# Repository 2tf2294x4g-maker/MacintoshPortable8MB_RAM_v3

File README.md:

# Mac Portable 8MB RAM Card (v3 — All-5V)

Expands a Macintosh Portable to **9 MB total** (1 MB onboard + 8 MB this card) — the maximum the Portable's address space supports.

All-5V design using 1M×8 SRAM chips and an ATF1502ASL CPLD. Works with both the **M5120** (non-backlit) and **M5126** (backlit) Portable via the MODEL jumper. Banks are added sequentially — no jumpers needed as you populate.

> ⚠️ **PRE-PRODUCTION — NOT TESTED**
> This board has been designed and ordered but has not yet been assembled or validated on real hardware. Schematics, firmware, and Gerbers are provided as-is. Do not build for production use until hardware validation is complete.

---

## What's new in v3 vs v2

| | v2 | v3 |
|---|---|---|
| Model compatibility | M5120 only | M5120 + M5126 (MODEL jumper) |
| Bank indicator | none | 4 green latching LEDs (one per bank) |
| Ghost RAM protection | none | 10 KΩ pull-downs on SD0–SD15 |
| Population jumper | SIZE jumper (JP1) | none — sequential by design |
| DTACK output | bodge wire to CPLD pad | J3 header (pin 1 = /DTACK, pin 2 = /EXT_DTACK) |
| SRAM count | 8× AS6C8008 | 8× AS6C8008 (same chips) |

---

## Specs

| | |
|---|---|
| Capacity | 8 MB (8× 1M×8 SRAM) |
| System total | 9 MB M5120 (open) / 7 MB M5126 (closed) |
| Bus width | 16-bit (two 8-bit SRAMs per bank) |
| Banks | 4 × 2 MB, populated sequentially |
| Logic | ATF1502ASL CPLD (5V, TQFP-44) |
| SRAM | 8× AS6C8008-55ZIN (5V, TSOP-II-44) |
| Layers | 4 (F.Cu signal / GND plane / +5V plane / B.Cu signal) |
| Connector | Samtec BCS-125-F-D-HE (50-pin 2×25, horizontal entry) |
| MODEL jumper | JP1: OPEN = M5120 non-backlit (9 MB) / CLOSED = M5126 backlit (7 MB) |

---

## Bill of Materials

| Ref | Qty | Value | Package | Part / Notes |
|-----|----:|-------|---------|--------------|
| U1–U8 | 8 | AS6C8008-55ZIN | TSOP-II-44 | Alliance Memory — 1M×8 5V SRAM 55 ns. Order spares. |
| U9 | 1 | ATF1502ASL | TQFP-44 | Microchip ATF1502ASL-**25AU44** — must be **ASL** (5V), not ASV |
| U10, U11 | 2 | 74HC245 | SOIC-20 **wide** | SN74HC245**DW** — verify wide (7.5 mm) body |
| J1 | 1 | RAM connector | Samtec BCS-125-F-D-HE | 50-pin socket, horizontal entry |
| J2 | 1 | JTAG header | 1×6 2.54 mm pin header | GND/VCC/TDO/TDI/TMS/TCK left-to-right |
| J3 | 1 | PDS DTACK header | 1×2 2.54 mm pin header | Pin 1 = /DTACK → PDS B7, Pin 2 = /EXT_DTACK → PDS B30 |
| JP1 | 1 | MODEL jumper | 1×2 2.54 mm pin header + shunt | OPEN = M5120 / CLOSED = M5126 |
| D1–D4 | 4 | Green LED | 0603 | Latch ON at boot when each bank is confirmed by the CPLD |
| R1–R4 | 4 | 330 Ω | 0402 | Series resistors for D1–D4 |
| R5–R20 | 16 | 10 KΩ | 0402 | Pull-downs on SD0–SD15 (SRAM side of 74HC245) — prevent ghost RAM |
| R21–R24 | 4 | 10 KΩ | 0805 | Pull-ups on CPLD unused inputs and MODEL jumper pin |
| C1–C14 | 14 | 100 nF | 0805 | X7R 50V ceramic bypass (one per IC) |
| C15–C19 | 5 | 10 µF | 0805 | X5R 16V ceramic bulk |

Full BOM: [PortableRAM-8MB-v3-BOM.csv](PortableRAM-8MB-v3-BOM.csv)

---

## ⚠️ Important — SRAM Pinout

The AS6C8008 (1M×8) and AS7C4096A (512K×8 used in the 4MB card) are **both TSOP-II-44 but have different pinouts**. Do not mix them between boards.

---

## Population Guide

Banks are populated sequentially — each pair of SRAMs adds 2 MB. No jumpers required.

| Step | Chips | Total RAM |
|------|-------|-----------|
| 1 | U1 + U5 | 2 MB |
| 2 | U2 + U6 | 4 MB |
| 3 | U3 + U7 | 6 MB |
| 4 | U4 + U8 | 8 MB |

The green LED for each bank (D1–D4) latches on at boot when the CPLD confirms that bank is active. A dark LED means the bank is not yet populated.

---

## MODEL Jumper (JP1)

| JP1 | Portable model | System RAM |
|-----|---------------|-----------|
| Open (no shunt) | M5120 non-backlit | 9 MB |
| Closed (shunt installed) | M5126 backlit | 7 MB |

The M5126 uses slot CS0 for its backlight controller, which conflicts with the top 2 MB bank. Closing JP1 disables that bank so the two don't fight. Leave open for M5120.

---

## Files

```
PortableRAM-8MB.kicad_pcb     — PCB layout (KiCad 9)
PortableRAM-8MB.kicad_sch     — Schematic
PortableRAM-8MB.kicad_pro     — Project file
PortableRAM.kicad_sym         — Custom symbol library
PortableRAM.pretty/           — Custom footprint library
Library.pretty/               — Additional footprints
Gerbers/                      — Gerber + drill files (ready to order)
PortableRAM-8MB-v3-Gerbers.zip — Same, zipped (upload directly to fab)
firmware/
  PortableRAM8_v3.pld            — CUPL source (ATF1502ASL logic)
  PortableRAM8_v3.jed            — Compiled JEDEC fusemap
  PortableRAM8_v3.svf            — SVF for OpenOCD programming
  PortableRAM8_v3.fit            — WinCUPL fit report
  program.sh                  — One-command programming script (Tigard)
  BUILD.md                    — Firmware build instructions (WinCUPL + Wine)
PortableRAM-8MB-v3-BOM.csv
```

---

## Ordering the PCB

Upload `PortableRAM-8MB-v3-Gerbers.zip` to your preferred fab (JLCPCB, PCBWay, OSHPark, etc.).

**Board settings:**
- Layers: **4**
- Thickness: 1.6 mm
- Surface finish: **ENIG** (recommended — fine-pitch 0.8 mm pads on TSOP-II-44 and TQFP-44)
- All other settings: fab defaults

---

## Assembly Notes

Solder in this order:

1. **U9** (ATF1502ASL CPLD, TQFP-44) — center first, then drag-solder
2. **U1–U8** (SRAM, TSOP-II-44) — fine pitch; flux generously. Populate in bank pairs: U1+U5 → U2+U6 → U3+U7 → U4+U8
3. **U10, U11** (74HC245, SOIC-20 wide)
4. **R5–R20** (10 KΩ 0402 pull-downs)
5. **R1–R4** (330 Ω 0402 LED resistors)
6. **R21–R24** (10 KΩ 0805 pull-ups)
7. **C1–C14** (100 nF 0805 bypass caps)
8. **C15–C19** (10 µF 0805 bulk caps)
9. **D1–D4** (green 0603 LEDs — observe polarity)
10. **JP1** (1×2 header — add shunt for M5126, leave open for M5120)
11. **J2** (1×6 JTAG header)
12. **J3** (1×2 PDS DTACK header — on board edge)
13. **J1** (Samtec connector) — last

---

## Programming the CPLD

The ATF1502ASL must be programmed before the card will work. Use J2 (1×6 header on the board edge).

### J2 pinout (left to right, component side)

| Pin | Signal |
|-----|--------|
| 1 | GND |
| 2 | VCC |
| 3 | TDO |
| 4 | TDI |
| 5 | TMS |
| 6 | TCK |

### With a Tigard programmer (FT2232H-based)

Set the Tigard voltage jumper to **5V** before connecting.

```bash
cd firmware
./program.sh PortableRAM8_v3.svf
```

Success output ends with `shutdown command invoked` and no TDO mismatch errors.

See [firmware/BUILD.md](firmware/BUILD.md) for the full build and programming pipeline (WinCUPL + Wine on Linux, prjbureau for SVF generation).

---

## Installation

1. Power off and unplug the Mac Portable.
2. Remove the battery and bottom cover.
3. Set JP1 (MODEL jumper) for your machine — open for M5120, closed for M5126.
4. Seat the card on the RAM expansion header — J1 is a friction-fit horizontal-entry socket.
5. Reassemble and power on.

With a full build (all 8 SRAMs), you should see **9 MB** in About This Macintosh (M5120) or **7 MB** (M5126). All four green LEDs D1–D4 will be lit.

### DTACK Performance Fix — J3 header

The Mac Portable's GLU chip generates /DTACK for the 68000 with region-dependent timing:

| Address range | GLU /DTACK | Condition |
|---|---|---|
| 0x000000–0x4FFFFF | 2 clocks | Always — hardwired fast path |
| 0x500000–0x8FFFFF | 6 clocks | Normal operation (register configured) |
| 0x500000–0x8FFFFF | 18 clocks | After sleep/wake (register reset) |

The 8 MB card spans 0x100000–0x8FFFFF, straddling the split. Banks 0–1 (0x100000–0x4FFFFF) already get the GLU's 2-clock fast path. Banks 2–3 (0x500000–0x8FFFFF) run at 6 clocks and collapse to 18 clocks after sleep/wake when the GLU's DTACK register loses its configuration.

The fix is built into v3: the CPLD asserts /DTACK directly via **J3 pin 1**, bypassing the GLU for all card accesses. Connect a wire from J3 pin 1 to **PDS slot pin B7** (/DTACK) on the Mac Portable motherboard. The CPLD's path is purely combinatorial — faster than even the GLU's 2-clock mode — and immune to sleep/wake state loss.

J3 pin 2 (/EXT_DTACK → PDS B30) is an optional second output for experimentation.

**Validated on v2 hardware (July 2026):**

| Configuration | Speedometer | Snooper | Post-sleep |
|---|---|---|---|
| 1 MB card (baseline) | 1.990 | 87% | 1.985 |
| 8 MB card — no DTACK fix | 1.486 | 51% | 0.974 / 22% |
| **8 MB card + CPLD DTACK** | **2.170** | **102%** | **2.170** |
| **4 MB card + CPLD DTACK** | **2.170** | **102%** | **2.170** |

The CPLD outperforms the GLU's fastest mode (102% vs 87% baseline) because its combinatorial propagation delay is well under one bus clock. Post-sleep collapse is fully eliminated. The 4 MB result confirms the CPLD path is faster than even the GLU's hardwired 2-clock mode — the fix benefits all bank configurations, not just the upper 8 MB range.

The PDS connector is the 96-pin DIN-41612 on the Mac Portable motherboard (3 rows A/B/C, 32 pins each). Pin B7 is in row B, position 7 from the component side.

---

## References & Acknowledgements

**Dynamic Engineering Mac Portable RAM Card**
The address decode and bus control logic in `PortableRAM8_v3.pld` is derived from GAL22V10 PLD source files originally written for the Dynamic Engineering commercial RAM expansion card. These files define the core signal equations — bank chip-select generation, byte-lane write control via UDS*/LDS*, bus transceiver direction, and output enable timing. The original `.PLD` files were recovered and shared by *techknight* on the TinkerDifferent forum and #skunkworks Discord. Translated here from three GAL22V10 chips to a single ATF1502ASL CPLD, with corrections to the `r_w_u` equation and address decode base, and extended for 8MB capacity and M5126 compatibility.

**miejas — Macintosh Portable 4MB Memory Expansion**
[https://github.com/miejas/Macintosh-Portable-4-MB-Memory-Expansion](https://github.com/miejas/Macintosh-Portable-4-MB-Memory-Expansion)
Open-source 4MB RAM card used as a cross-reference for connector pinout, bus transceiver approach, and firmware structure.

**Reza Fouladian — PortableRAM BGA 8MB**
[https://github.com/rezafouladian/PortableRAM-BGA-8MB](https://github.com/rezafouladian/PortableRAM-BGA-8MB)
BGA-format 8MB card using the ATF1502ASV (3.3V CPLD) and SN74LVC4245A level translators. Reference for the 8MB address decode strategy and CPLD pin planning. Reza also provided direct guidance on driving /DTACK from the CPLD and on the Mac Portable PDS connector pinout — specifically confirming that /DTACK is available on PDS pin B7 and can be driven directly from a CPLD output. This insight is the basis for the J3 DTACK header on v3 and the validated bodge fix on v2.

**Apple Mac Portable Developer Notes & Schematics**
Apple's original hardware documentation for the Mac Portable expansion bus, memory map, and GLU register behaviour (including the $FC0200 DTACK register).

---

## License

Hardware released under [CERN-OHL-S v2](https://ohwr.org/cern_ohl_s_v2.txt). Firmware source (`PortableRAM8_v3.pld`) released under MIT.

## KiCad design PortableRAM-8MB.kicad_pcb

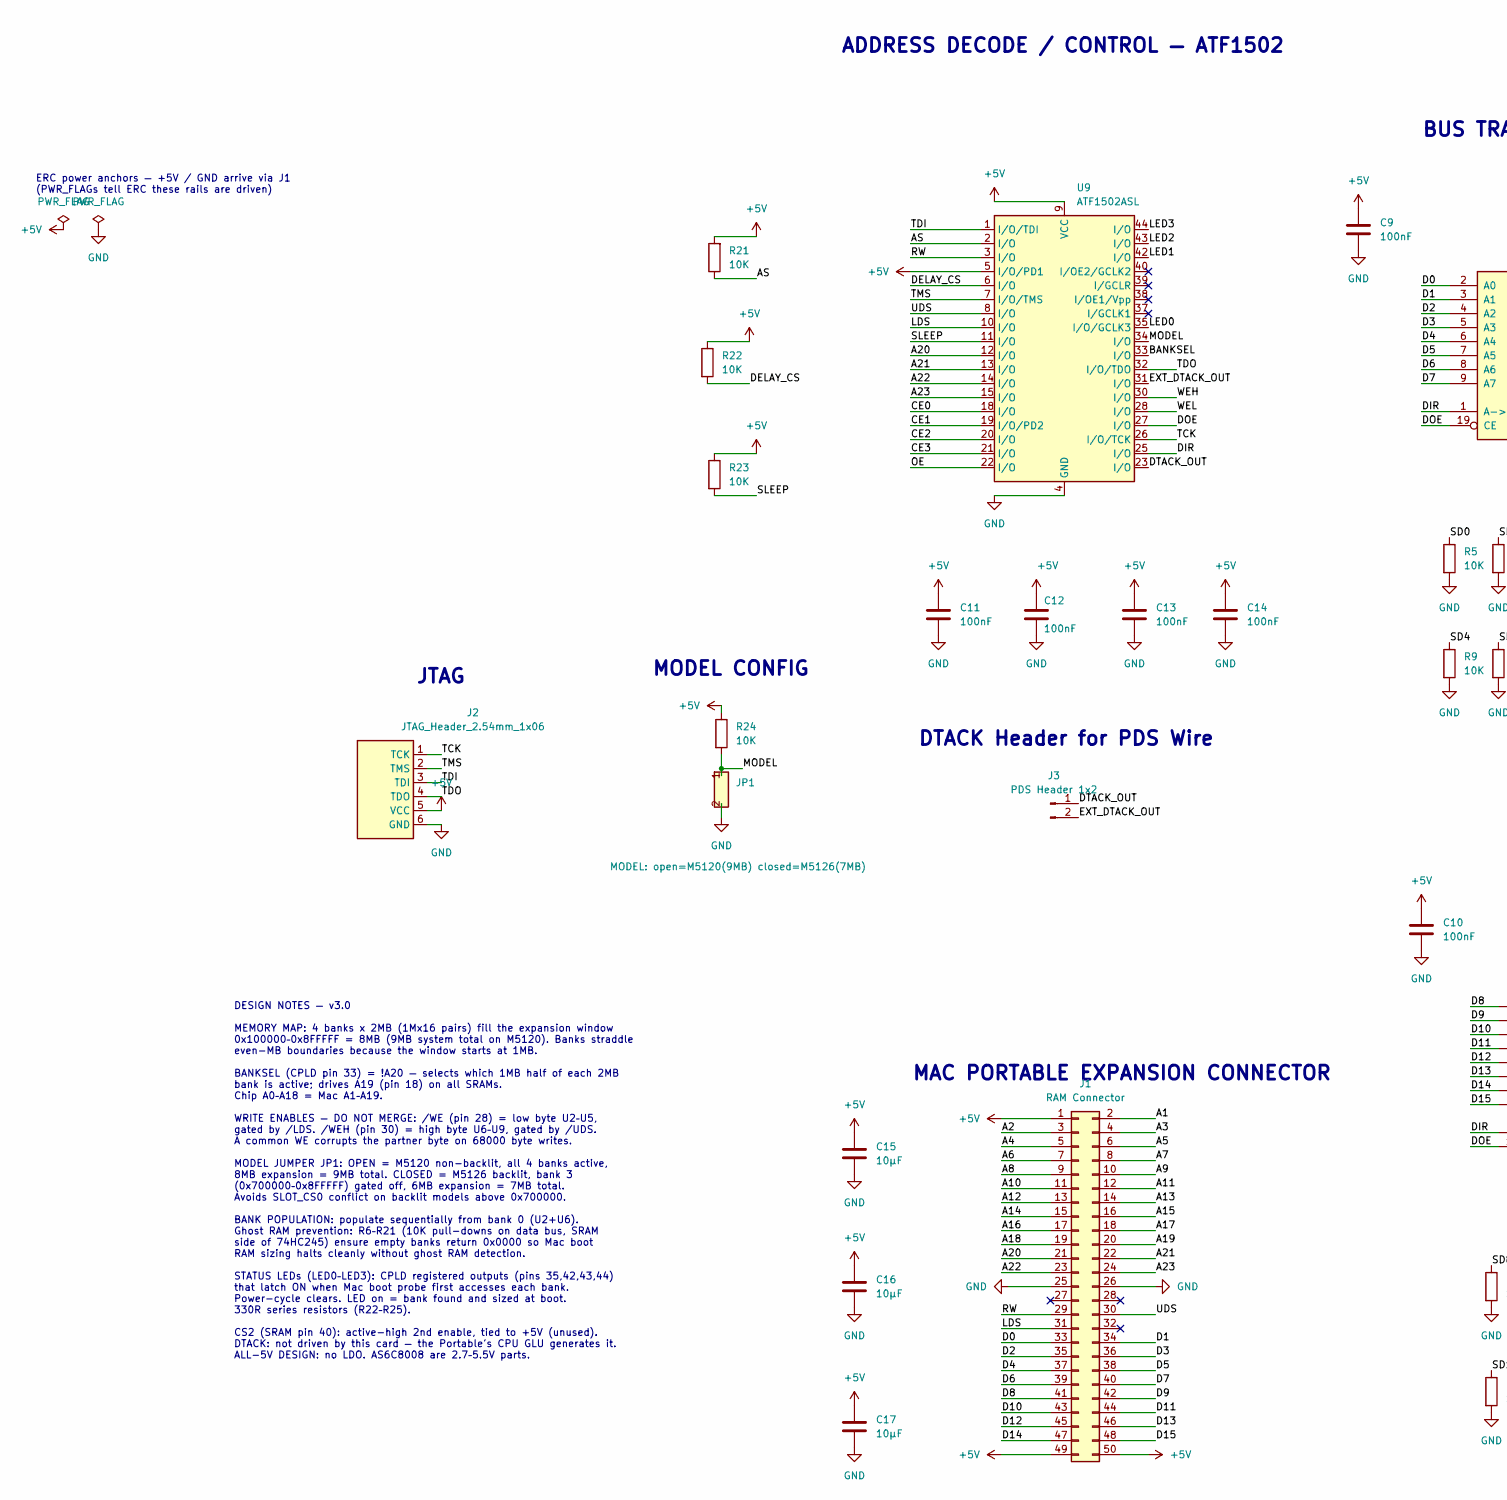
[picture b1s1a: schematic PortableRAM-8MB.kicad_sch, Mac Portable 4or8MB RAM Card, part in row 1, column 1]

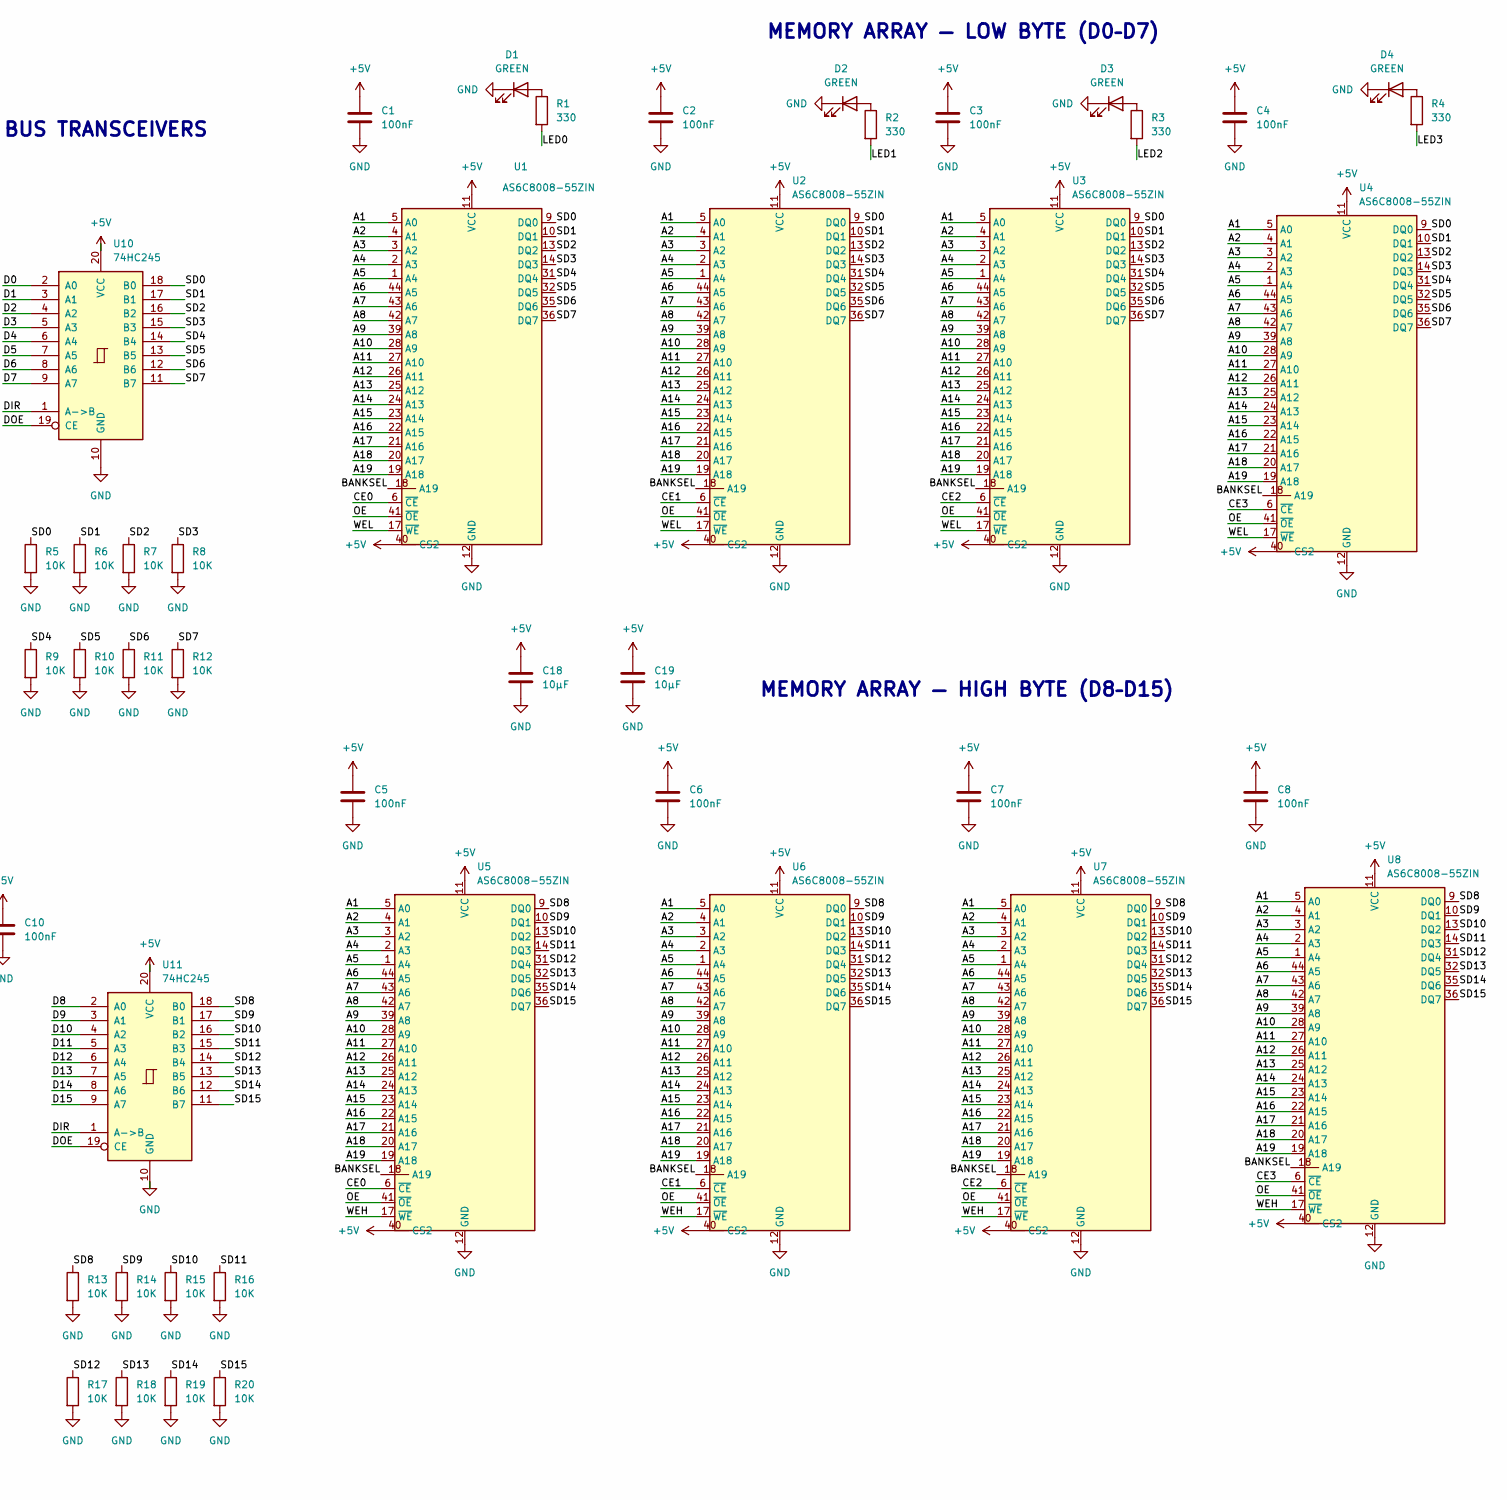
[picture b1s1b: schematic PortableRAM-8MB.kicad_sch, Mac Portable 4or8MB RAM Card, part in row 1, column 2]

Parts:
C1, C2, C3, C4, C5, C6, C7, C8, C9, C10, C11, C12, C13, C14: 100nF; C_0805_2012Metric
C15, C16, C17, C18, C19: 10µF; C_0805_2012Metric
D1, D2, D3, D4: GREEN; LED_0603_1608Metric
J1: RAM Connector; Samtec_BCS-125-F-D-HE
J2: JTAG_Header_2.54mm_1x06; PinHeader_1x06_P2.54mm_Vertical
J3: PDS Header 1x2; PinHeader_1x02_P2.54mm_Vertical
JP1: MODEL: open=M5120(9MB) closed=M5126(7MB); PinHeader_1x02_P2.54mm_Vertical
R1, R2, R3, R4: 330; R_0402_1005Metric
R5, R6, R7, R8, R9, R10, R11, R12, R13, R14, R15, R16, R17, R18, R19, R20: 10K; R_0402_1005Metric
R21, R22, R23, R24: 10K; R_0805_2012Metric
U1, U2, U3, U4, U5, U6, U7, U8: AS6C8008-55ZIN; TSOP-II-44_10.16x18.41mm_P0.8mm
U9: ATF1502ASL; TQFP-44_10x10mm_P0.8mm
U10, U11: 74HC245; SOIC-20W_7.5x12.8mm_P1.27mm

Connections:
+5V: C1.1, C2.1, C3.1, C4.1, C5.1, C6.1, C7.1, C8.1, C9.1, C10.1, C11.1, C12.1, C13.1, C14.1, C15.1, C16.1, C17.1, C18.1, C19.1, J1.1, J1.49, J1.50, J2.5 (VCC), R21.2, R22.1, R23.1, R24.1, U1.11 (VCC), U1.33 (VCC), U1.40 (CS2), U2.11 (VCC), U2.33 (VCC), U2.40 (CS2), U3.11 (VCC), U3.33 (VCC), U3.40 (CS2), U4.11 (VCC), U4.33 (VCC), U4.40 (CS2), U5.11 (VCC), U5.33 (VCC), U5.40 (CS2), U6.11 (VCC), U6.33 (VCC), U6.40 (CS2), U7.11 (VCC), U7.33 (VCC), U7.40 (CS2), U8.11 (VCC), U8.33 (VCC), U8.40 (CS2), U9.5 (I/O/PD1), U9.9 (VCC), U9.17 (VCC), U9.29 (VCC), U9.41 (VCC), U10.20 (VCC), U11.20 (VCC)
/A1: J1.2, U1.5 (A0), U2.5 (A0), U3.5 (A0), U4.5 (A0), U5.5 (A0), U6.5 (A0), U7.5 (A0), U8.5 (A0)
/A2: J1.3, U1.4 (A1), U2.4 (A1), U3.4 (A1), U4.4 (A1), U5.4 (A1), U6.4 (A1), U7.4 (A1), U8.4 (A1)
/A3: J1.4, U1.3 (A2), U2.3 (A2), U3.3 (A2), U4.3 (A2), U5.3 (A2), U6.3 (A2), U7.3 (A2), U8.3 (A2)
/A4: J1.5, U1.2 (A3), U2.2 (A3), U3.2 (A3), U4.2 (A3), U5.2 (A3), U6.2 (A3), U7.2 (A3), U8.2 (A3)
/A5: J1.6, U1.1 (A4), U2.1 (A4), U3.1 (A4), U4.1 (A4), U5.1 (A4), U6.1 (A4), U7.1 (A4), U8.1 (A4)
/A6: J1.7, U1.44 (A5), U2.44 (A5), U3.44 (A5), U4.44 (A5), U5.44 (A5), U6.44 (A5), U7.44 (A5), U8.44 (A5)
/A7: J1.8, U1.43 (A6), U2.43 (A6), U3.43 (A6), U4.43 (A6), U5.43 (A6), U6.43 (A6), U7.43 (A6), U8.43 (A6)
/A8: J1.9, U1.42 (A7), U2.42 (A7), U3.42 (A7), U4.42 (A7), U5.42 (A7), U6.42 (A7), U7.42 (A7), U8.42 (A7)
/A9: J1.10, U1.39 (A8), U2.39 (A8), U3.39 (A8), U4.39 (A8), U5.39 (A8), U6.39 (A8), U7.39 (A8), U8.39 (A8)
/A10: J1.11, U1.28 (A9), U2.28 (A9), U3.28 (A9), U4.28 (A9), U5.28 (A9), U6.28 (A9), U7.28 (A9), U8.28 (A9)
/A11: J1.12, U1.27 (A10), U2.27 (A10), U3.27 (A10), U4.27 (A10), U5.27 (A10), U6.27 (A10), U7.27 (A10), U8.27 (A10)
/A12: J1.13, U1.26 (A11), U2.26 (A11), U3.26 (A11), U4.26 (A11), U5.26 (A11), U6.26 (A11), U7.26 (A11), U8.26 (A11)
/A13: J1.14, U1.25 (A12), U2.25 (A12), U3.25 (A12), U4.25 (A12), U5.25 (A12), U6.25 (A12), U7.25 (A12), U8.25 (A12)
/A14: J1.15, U1.24 (A13), U2.24 (A13), U3.24 (A13), U4.24 (A13), U5.24 (A13), U6.24 (A13), U7.24 (A13), U8.24 (A13)
/A15: J1.16, U1.23 (A14), U2.23 (A14), U3.23 (A14), U4.23 (A14), U5.23 (A14), U6.23 (A14), U7.23 (A14), U8.23 (A14)
/A16: J1.17, U1.22 (A15), U2.22 (A15), U3.22 (A15), U4.22 (A15), U5.22 (A15), U6.22 (A15), U7.22 (A15), U8.22 (A15)
/A17: J1.18, U1.21 (A16), U2.21 (A16), U3.21 (A16), U4.21 (A16), U5.21 (A16), U6.21 (A16), U7.21 (A16), U8.21 (A16)
/A18: J1.19, U1.20 (A17), U2.20 (A17), U3.20 (A17), U4.20 (A17), U5.20 (A17), U6.20 (A17), U7.20 (A17), U8.20 (A17)
/A19: J1.20, U1.19 (A18), U2.19 (A18), U3.19 (A18), U4.19 (A18), U5.19 (A18), U6.19 (A18), U7.19 (A18), U8.19 (A18)
/A20: J1.21, U9.12 (I/O)
/A21: J1.22, U9.13 (I/O)
/A22: J1.23, U9.14 (I/O)
/A23: J1.24, U9.15 (I/O)
/AS: R21.1, U9.2 (I/O)
/BANKSEL: U1.18 (A19), U2.18 (A19), U3.18 (A19), U4.18 (A19), U5.18 (A19), U6.18 (A19), U7.18 (A19), U8.18 (A19), U9.33 (I/O)
/CE0: U1.6 (~CE), U5.6 (~CE), U9.18 (I/O)
/CE1: U2.6 (~CE), U6.6 (~CE), U9.19 (I/O/PD2)
/CE2: U3.6 (~CE), U7.6 (~CE), U9.20 (I/O)
/CE3: U4.6 (~CE), U8.6 (~CE), U9.21 (I/O)
/D0: J1.33, U10.2 (A0)
/D1: J1.34, U10.3 (A1)
/D2: J1.35, U10.4 (A2)
/D3: J1.36, U10.5 (A3)
/D4: J1.37, U10.6 (A4)
/D5: J1.38, U10.7 (A5)
/D6: J1.39, U10.8 (A6)
/D7: J1.40, U10.9 (A7)
/D8: J1.41, U11.2 (A0)
/D9: J1.42, U11.3 (A1)
/D10: J1.43, U11.4 (A2)
/D11: J1.44, U11.5 (A3)
/D12: J1.45, U11.6 (A4)
/D13: J1.46, U11.7 (A5)
/D14: J1.47, U11.8 (A6)
/D15: J1.48, U11.9 (A7)
/DELAY_CS: R22.2, U9.6 (I/O)
/DIR: U9.25 (I/O), U10.1 (A->B), U11.1 (A->B)
/DOE: U9.27 (I/O), U10.19 (CE), U11.19 (CE)
/DTACK_OUT: J3.1, U9.23 (I/O)
/EXT_DTACK_OUT: J3.2, U9.31 (I/O)
/LDS: J1.31, U9.10 (I/O)
/LED0: R1.2, U9.35 (I/O/GCLK3)
/LED1: R2.2, U9.42 (I/O)
/LED2: R3.2, U9.43 (I/O)
/LED3: R4.2, U9.44 (I/O)
/MODEL: JP1.1, R24.2, U9.34 (I/O)
/OE: U1.41 (~OE), U2.41 (~OE), U3.41 (~OE), U4.41 (~OE), U5.41 (~OE), U6.41 (~OE), U7.41 (~OE), U8.41 (~OE), U9.22 (I/O)
/RW: J1.29, U9.3 (I/O)
/SD0: R5.1, U1.9 (DQ0), U2.9 (DQ0), U3.9 (DQ0), U4.9 (DQ0), U10.18 (B0)
/SD1: R6.1, U1.10 (DQ1), U2.10 (DQ1), U3.10 (DQ1), U4.10 (DQ1), U10.17 (B1)
/SD2: R7.1, U1.13 (DQ2), U2.13 (DQ2), U3.13 (DQ2), U4.13 (DQ2), U10.16 (B2)
/SD3: R8.1, U1.14 (DQ3), U2.14 (DQ3), U3.14 (DQ3), U4.14 (DQ3), U10.15 (B3)
/SD4: R9.1, U1.31 (DQ4), U2.31 (DQ4), U3.31 (DQ4), U4.31 (DQ4), U10.14 (B4)
/SD5: R10.1, U1.32 (DQ5), U2.32 (DQ5), U3.32 (DQ5), U4.32 (DQ5), U10.13 (B5)
/SD6: R11.1, U1.35 (DQ6), U2.35 (DQ6), U3.35 (DQ6), U4.35 (DQ6), U10.12 (B6)
/SD7: R12.1, U1.36 (DQ7), U2.36 (DQ7), U3.36 (DQ7), U4.36 (DQ7), U10.11 (B7)
/SD8: R13.1, U5.9 (DQ0), U6.9 (DQ0), U7.9 (DQ0), U8.9 (DQ0), U11.18 (B0)
/SD9: R14.1, U5.10 (DQ1), U6.10 (DQ1), U7.10 (DQ1), U8.10 (DQ1), U11.17 (B1)
/SD10: R15.1, U5.13 (DQ2), U6.13 (DQ2), U7.13 (DQ2), U8.13 (DQ2), U11.16 (B2)
/SD11: R16.1, U5.14 (DQ3), U6.14 (DQ3), U7.14 (DQ3), U8.14 (DQ3), U11.15 (B3)
/SD12: R17.1, U5.31 (DQ4), U6.31 (DQ4), U7.31 (DQ4), U8.31 (DQ4), U11.14 (B4)
/SD13: R18.1, U5.32 (DQ5), U6.32 (DQ5), U7.32 (DQ5), U8.32 (DQ5), U11.13 (B5)
/SD14: R19.1, U5.35 (DQ6), U6.35 (DQ6), U7.35 (DQ6), U8.35 (DQ6), U11.12 (B6)
/SD15: R20.1, U5.36 (DQ7), U6.36 (DQ7), U7.36 (DQ7), U8.36 (DQ7), U11.11 (B7)
/SLEEP: R23.2, U9.11 (I/O)
/TCK: J2.1 (TCK), U9.26 (I/O/TCK)
/TDI: J2.3 (TDI), U9.1 (I/O/TDI)
/TDO: J2.4 (TDO), U9.32 (I/O/TDO)
/TMS: J2.2 (TMS), U9.7 (I/O/TMS)
/UDS: J1.30, U9.8 (I/O)
/WEH: U5.17 (~WE), U6.17 (~WE), U7.17 (~WE), U8.17 (~WE), U9.30 (I/O)
/WEL: U1.17 (~WE), U2.17 (~WE), U3.17 (~WE), U4.17 (~WE), U9.28 (I/O)
GND: C1.2, C2.2, C3.2, C4.2, C5.2, C6.2, C7.2, C8.2, C9.2, C10.2, C11.2, C12.2, C13.2, C14.2, C15.2, C16.2, C17.2, C18.2, C19.2, D1.1 (K), D2.1 (K), D3.1 (K), D4.1 (K), J1.25, J1.26, J2.6 (GND), JP1.2, R5.2, R6.2, R7.2, R8.2, R9.2, R10.2, R11.2, R12.2, R13.2, R14.2, R15.2, R16.2, R17.2, R18.2, R19.2, R20.2, U1.12 (GND), U1.34 (GND), U2.12 (GND), U2.34 (GND), U3.12 (GND), U3.34 (GND), U4.12 (GND), U4.34 (GND), U5.12 (GND), U5.34 (GND), U6.12 (GND), U6.34 (GND), U7.12 (GND), U7.34 (GND), U8.12 (GND), U8.34 (GND), U9.4 (GND), U9.16 (GND), U9.24 (GND), U9.36 (GND), U10.10 (GND), U11.10 (GND); also elsewhere on the board
unnamed: D1.2 (A), R1.1
unnamed: D2.2 (A), R2.1
unnamed: D3.2 (A), R3.1
unnamed: D4.2 (A), R4.1

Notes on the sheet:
JTAG
MAC PORTABLE EXPANSION CONNECTOR
ADDRESS DECODE / CONTROL — ATF1502
BUS TRANSCEIVERS
MEMORY ARRAY — LOW BYTE (D0–D7)
DESIGN NOTES — v3.0 MEMORY MAP: 4 banks x 2MB (1Mx16 pairs) fill the expansion window 0x100000–0x8FFFFF = 8MB (9MB system total on M5120). Banks straddle even-MB boundaries because the window starts at 1MB. BANKSEL (CPLD pin 33) = !A20 — selects which 1MB half of each 2MB bank is active; drives A19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
MEMORY ARRAY — HIGH BYTE (D8–D15)
MODEL CONFIG
DTACK Header for PDS Wire
ERC power anchors — +5V / GND arrive via J1 (PWR_FLAGs tell ERC these rails are driven)

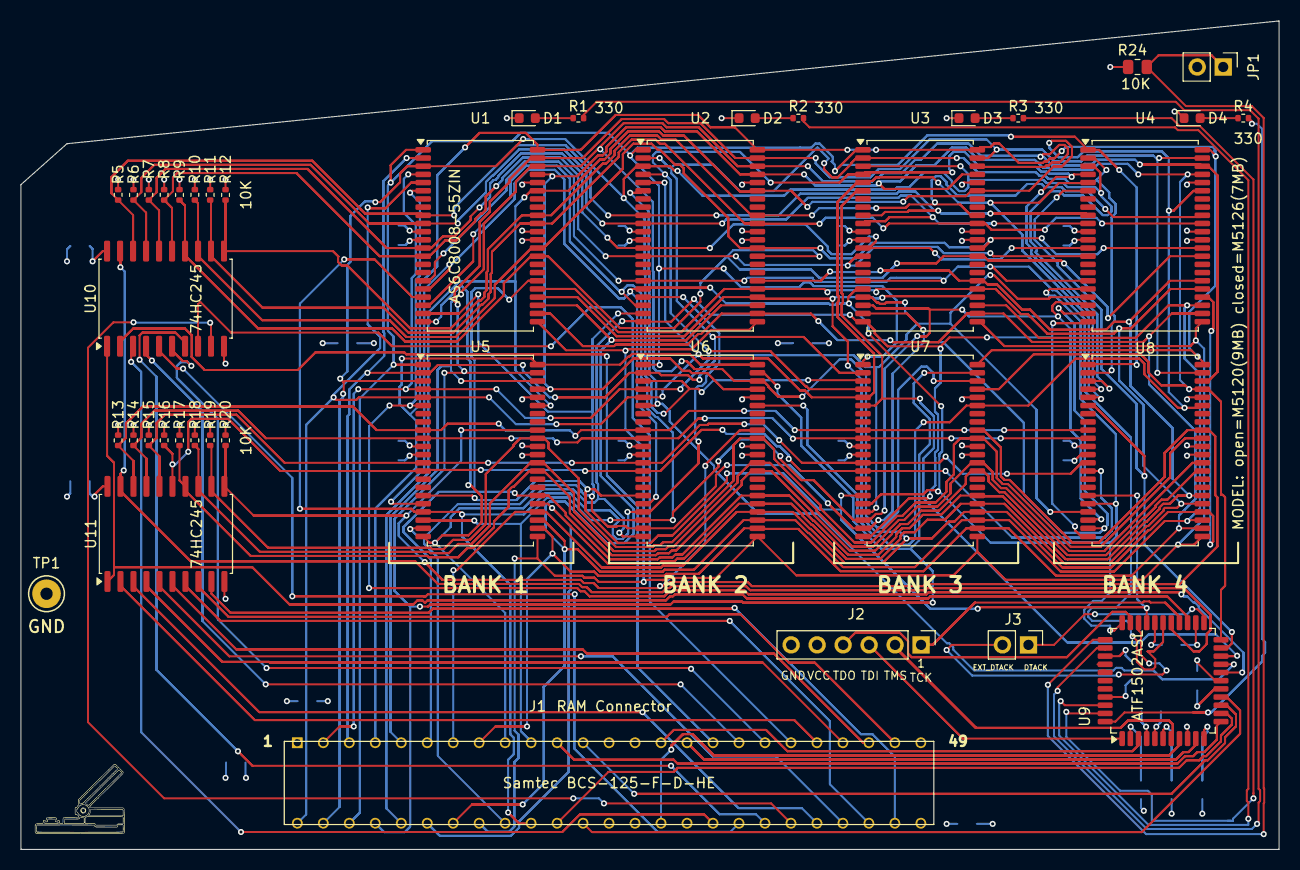
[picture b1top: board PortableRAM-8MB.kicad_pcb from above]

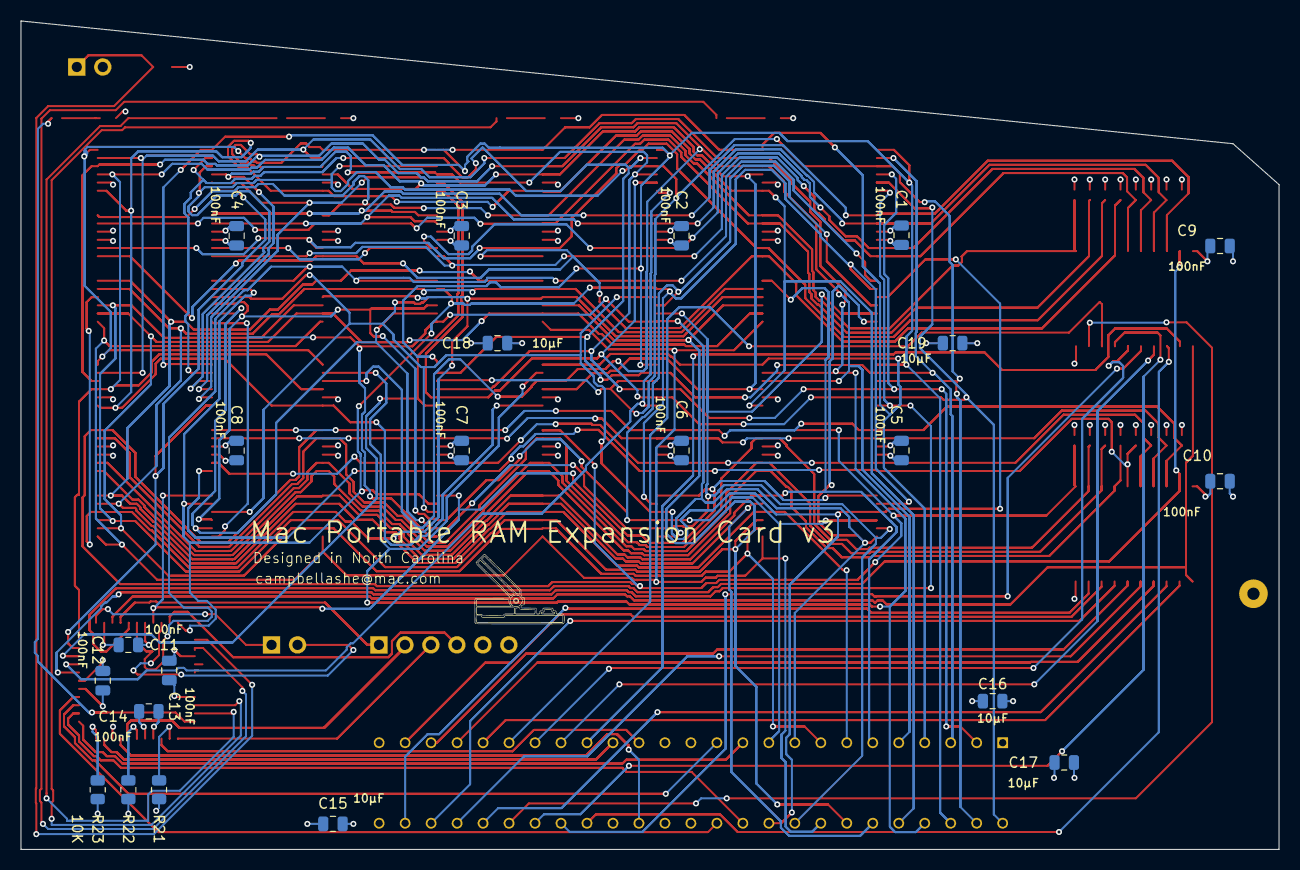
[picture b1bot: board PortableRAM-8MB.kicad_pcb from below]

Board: 4 copper layers, 123.0 x 81.0 mm, 63 parts (22 on the bottom side), 88 nets.

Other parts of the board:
TP1: GND; TestPoint_GND

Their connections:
GND: TP1.1; also elsewhere on the board

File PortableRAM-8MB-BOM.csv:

Ref,Qty,Value,Package,Manufacturer,Mfr Part Number,Notes
U1-U8,8,AS6C8008-55ZIN,TSOP-II-44 (10.16x18.41mm P0.8mm),Alliance Memory,AS6C8008-55ZIN,1Mx8 SRAM 5V 55ns (Z=TSOP-II pkg); ~$13-15 each; order 1-2 spares; populate sequentially: U1+U5=2MB U2+U6=4MB U3+U7=6MB U4+U8=8MB
U9,1,ATF1502ASL,TQFP-44 (10x10mm P0.8mm),Microchip,ATF1502ASL-25AU44,5V CPLD (ASL = 5V; do NOT order ASV which is 3.3V); program via J2 JTAG header; order a spare
U10 U11,2,74HC245,SOIC-20W (7.5mm wide),TI/Nexperia,SN74HC245DW,Octal bus transceiver 5V; verify WIDE SOIC-20 body (DW/DWR suffix)
J1,1,RAM Connector,Samtec BCS-125-F-D-HE,Samtec,BCS-125-F-D-HE,50-pin 2x25 2.54mm socket strip; footprint verified vs drawing
J2,1,JTAG Header 1x06,PinHeader 2.54mm 1x06 vertical,Generic,,GND/VCC/TDO/TDI/TMS/TCK left-to-right; labeled on silkscreen; for Tigard programmer
J3,1,PDS DTACK header 1x02,PinHeader 2.54mm 1x02 vertical,Generic,,Pin 1 = /DTACK -> PDS B7; Pin 2 = /EXT_DTACK -> PDS B30 (optional)
JP1,1,MODEL jumper 1x02,PinHeader 2.54mm 1x02 vertical,Generic,,OPEN=M5120 non-backlit (9MB total) / CLOSED=M5126 backlit (7MB total). Add one 2.54mm shunt.
D1-D4,4,GREEN LED,LED_0603 (1608 metric),Generic,,Green indicator LEDs; latch ON when Mac boot probe confirms each bank; board top edge
R1-R4,4,330,R_0402 (1005 metric),Generic,,Series resistors for D1-D4 LEDs; 330 ohm 1% 1/16W
R5-R20,16,10K,R_0402 (1005 metric),Generic,,Pull-down resistors on SD0-SD15 data bus (SRAM side of 74HC245); prevent ghost RAM on unpopulated banks
R21-R24,4,10K,R_0805 (2012 metric),Generic,,Pull-up resistors on CPLD unused inputs (/AS /DELAY_CS /SLEEP) and MODEL jumper JP1 pin; 5% thick film
C1-C14,14,100nF,C_0805 (2012 metric),Generic,,X7R 50V ceramic decoupling; one per SRAM + U9 + U10 + U11; buy strip of 50+
C15-C19,5,10uF,C_0805 (2012 metric),Generic,,X5R 16V ceramic bulk decoupling; buy 10+
